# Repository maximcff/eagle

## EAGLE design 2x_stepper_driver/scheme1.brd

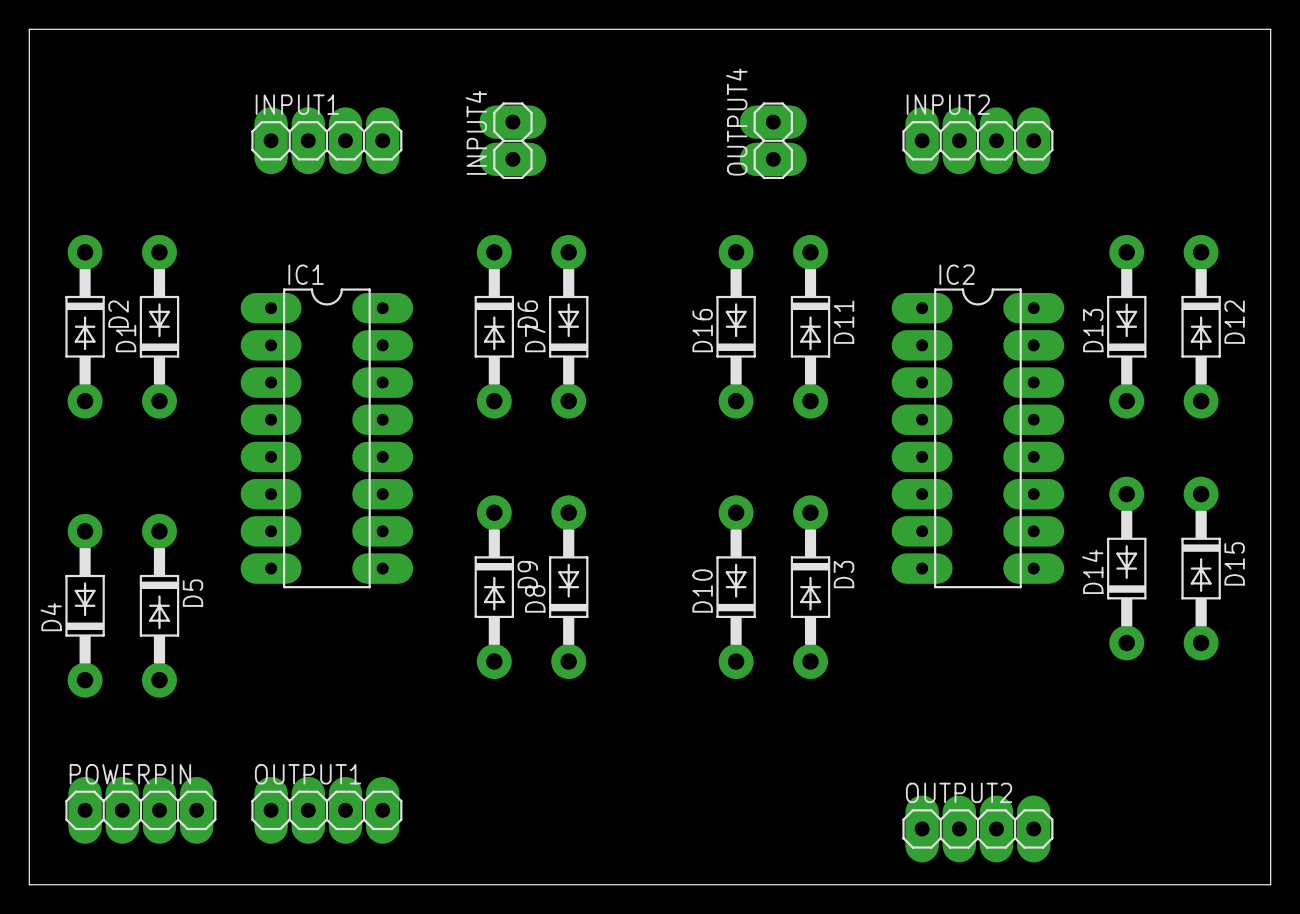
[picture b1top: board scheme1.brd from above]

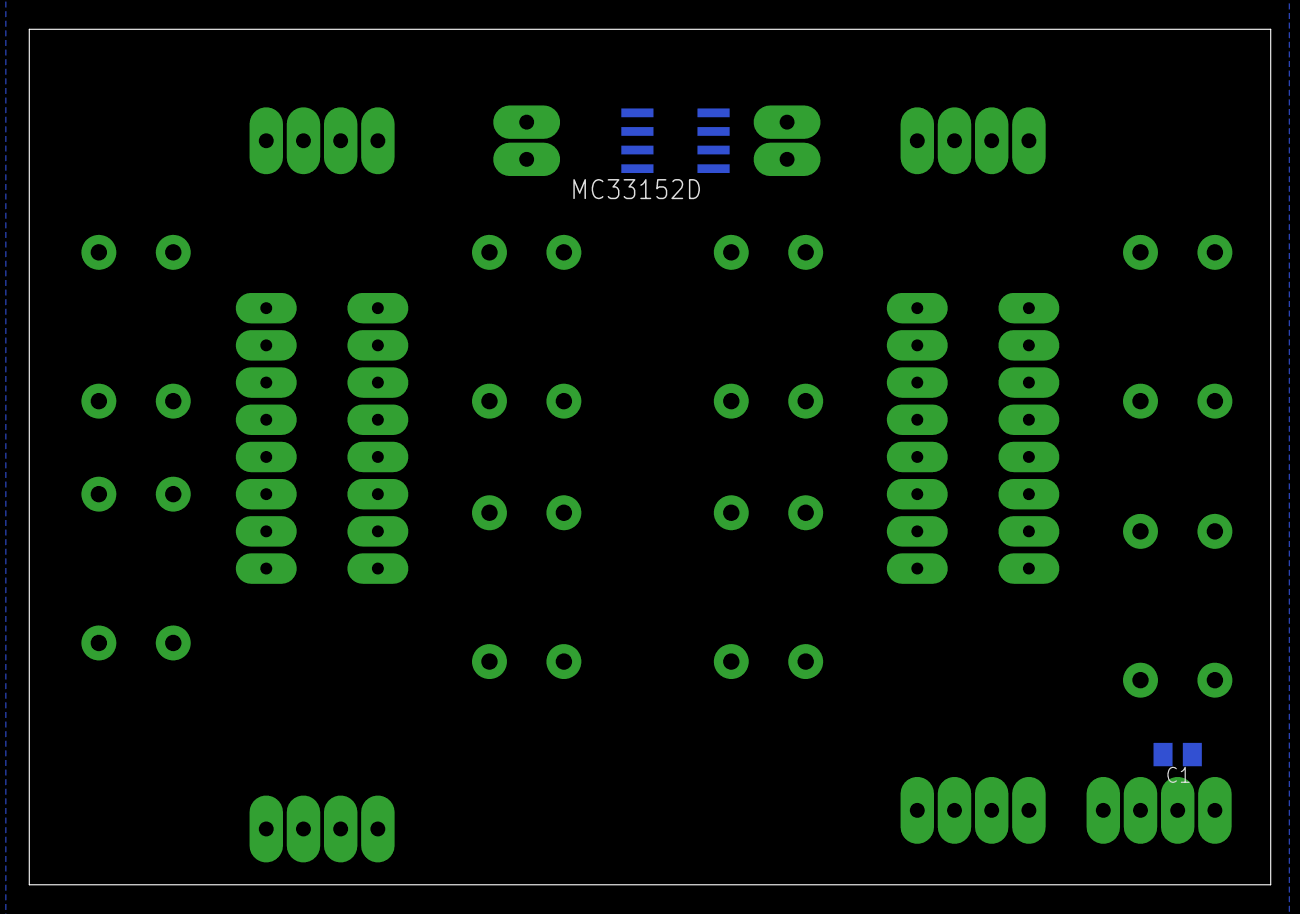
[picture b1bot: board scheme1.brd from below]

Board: 2 copper layers, 84.8 x 58.4 mm, 27 parts (2 on the bottom side), 23 nets, no tracks yet.

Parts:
C1: 0.22 uF; C0805K
D1, D2, D3, D4, D5, D6, D7, D8, D9, D10, D11, D12, D13, D14, D15, D16: 1N4933; DO41-10
IC1, IC2: L293E; DIL16
INPUT1, INPUT2: 1X04
INPUT4: 1X02
MC33152D: MC33152D; SOIC8
OUTPUT1, OUTPUT2: 1X04
OUTPUT4: 1X02
POWERPIN: 1X04

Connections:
+5V: IC1.1, IC1.9, IC1.16, IC2.1, IC2.9, IC2.16, POWERPIN.2
+12V: C1.1, D2.C, D4.C, D6.C, D8.C, D10.C, D11.C, D12.C, D14.C, IC1.8, IC2.8, MC33152D.6, POWERPIN.1
GND: C1.2, D1.A, D3.A, D5.A, D7.A, D9.A, D13.A, D15.A, D16.A, IC1.4, IC1.5, IC1.12, IC1.13, IC2.4, IC2.5, IC2.12, IC2.13, MC33152D.3, POWERPIN.3, POWERPIN.4
IN1: IC1.2, INPUT1.1
IN2: IC1.7, INPUT1.2
IN3: IC1.10, INPUT1.3
IN4: IC1.15, INPUT1.4
IN5: IC2.2, INPUT2.1
IN6: IC2.7, INPUT2.2
IN7: IC2.15, INPUT2.3
IN8: IC2.10, INPUT2.4
IN9: INPUT4.1, MC33152D.2
IN10: INPUT4.2, MC33152D.4
OUT1: D1.C, D2.A, IC1.3, OUTPUT1.1
OUT2: D4.A, D5.C, IC1.6, OUTPUT1.2
OUT3: D8.A, D9.C, IC1.11, OUTPUT1.3
OUT4: D6.A, D7.C, IC1.14, OUTPUT1.4
OUT5: D11.A, D16.C, IC2.3, OUTPUT2.1
OUT6: D3.C, D10.A, IC2.6, OUTPUT2.2
OUT7: D12.A, D13.C, IC2.14, OUTPUT2.3
OUT8: D14.A, D15.C, IC2.11, OUTPUT2.4
OUT9: MC33152D.7, OUTPUT4.1
OUT10: MC33152D.5, OUTPUT4.2

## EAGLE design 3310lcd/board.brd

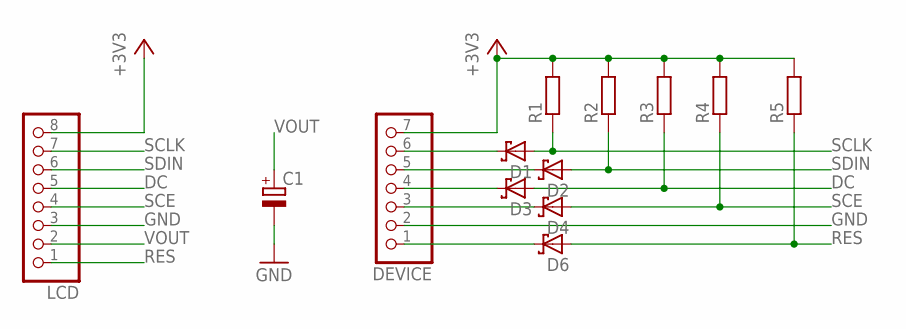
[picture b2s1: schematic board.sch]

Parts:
C1: CPOL-EUE2.5-5; E2,5-5
D1, D2, D3, D4, D6: SCHOTTKY-DIODESMD; SMB
DEVICE: PINHD-1X7; 1X07
LCD: PINHD-1X8; 1X08
R1, R2, R3, R4, R5: R-EU_R0805; R0805

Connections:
+3V3: DEVICE.7, LCD.8, R1.2, R2.2, R3.2, R4.2, R5.2
DC: D3.A, LCD.5, R3.1
GND: C1.-, DEVICE.2, LCD.3
unnamed: D1.C, DEVICE.6
unnamed: D2.C, DEVICE.5
unnamed: D3.C, DEVICE.4
unnamed: D4.C, DEVICE.3
unnamed: D6.C, DEVICE.1
RES: D6.A, LCD.1, R5.1
SCE: D4.A, LCD.4, R4.1
SCLK: D1.A, LCD.7, R1.1
SDIN: D2.A, LCD.6, R2.1
VOUT: C1.+, LCD.2

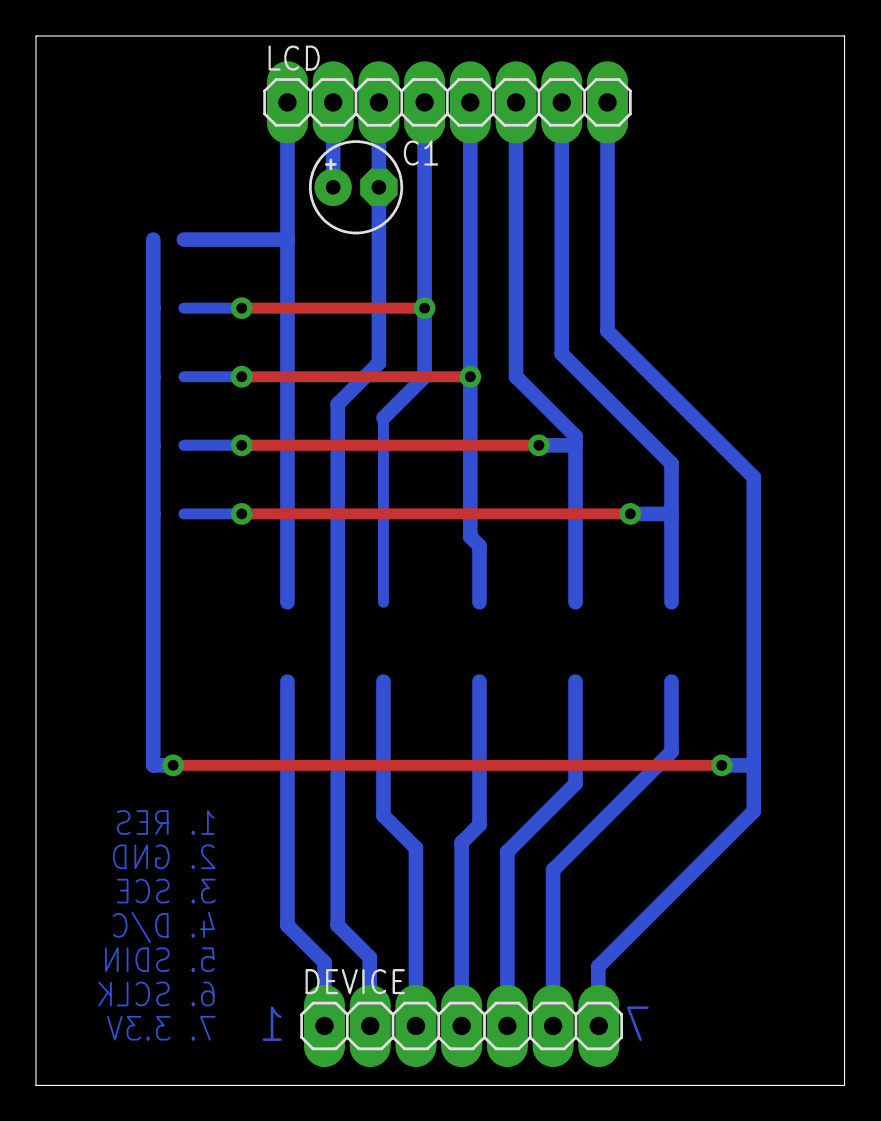
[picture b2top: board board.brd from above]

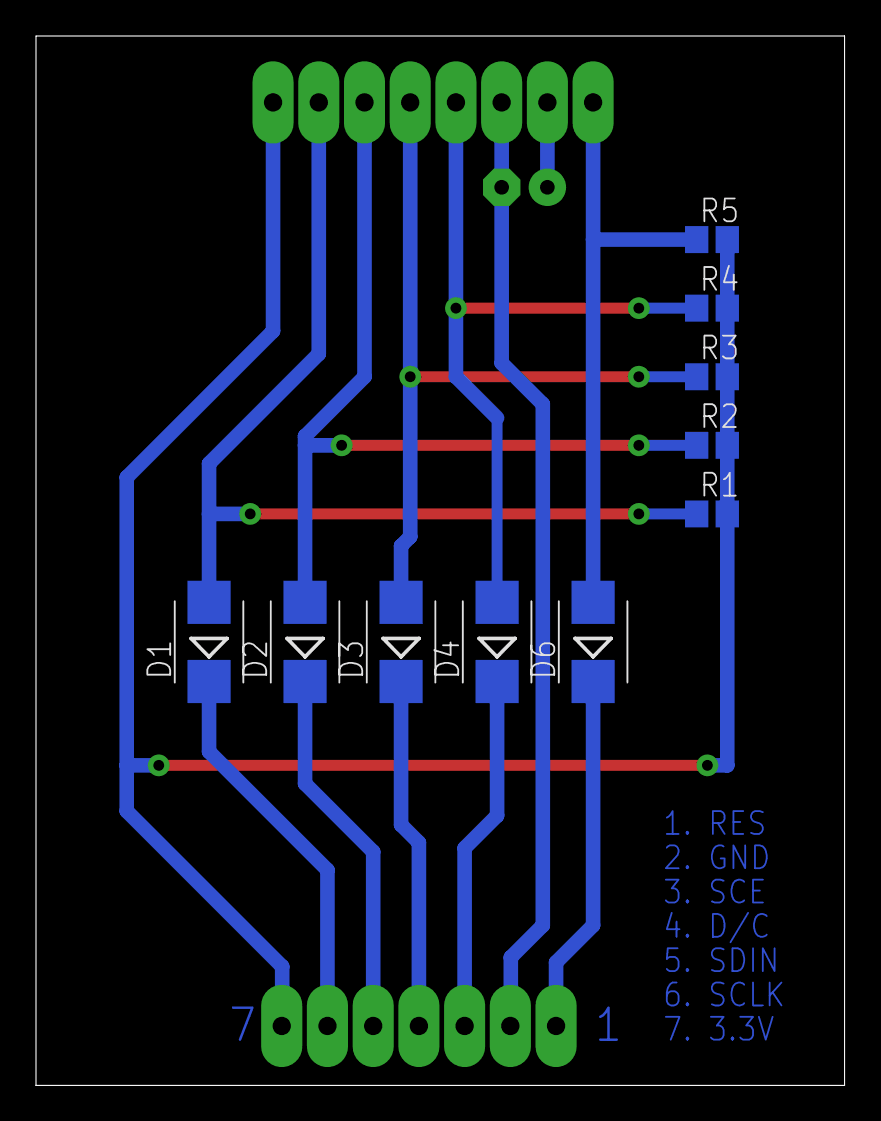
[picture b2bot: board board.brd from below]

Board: 2 copper layers, 44.9 x 58.3 mm, 13 parts (10 on the bottom side), 13 nets.

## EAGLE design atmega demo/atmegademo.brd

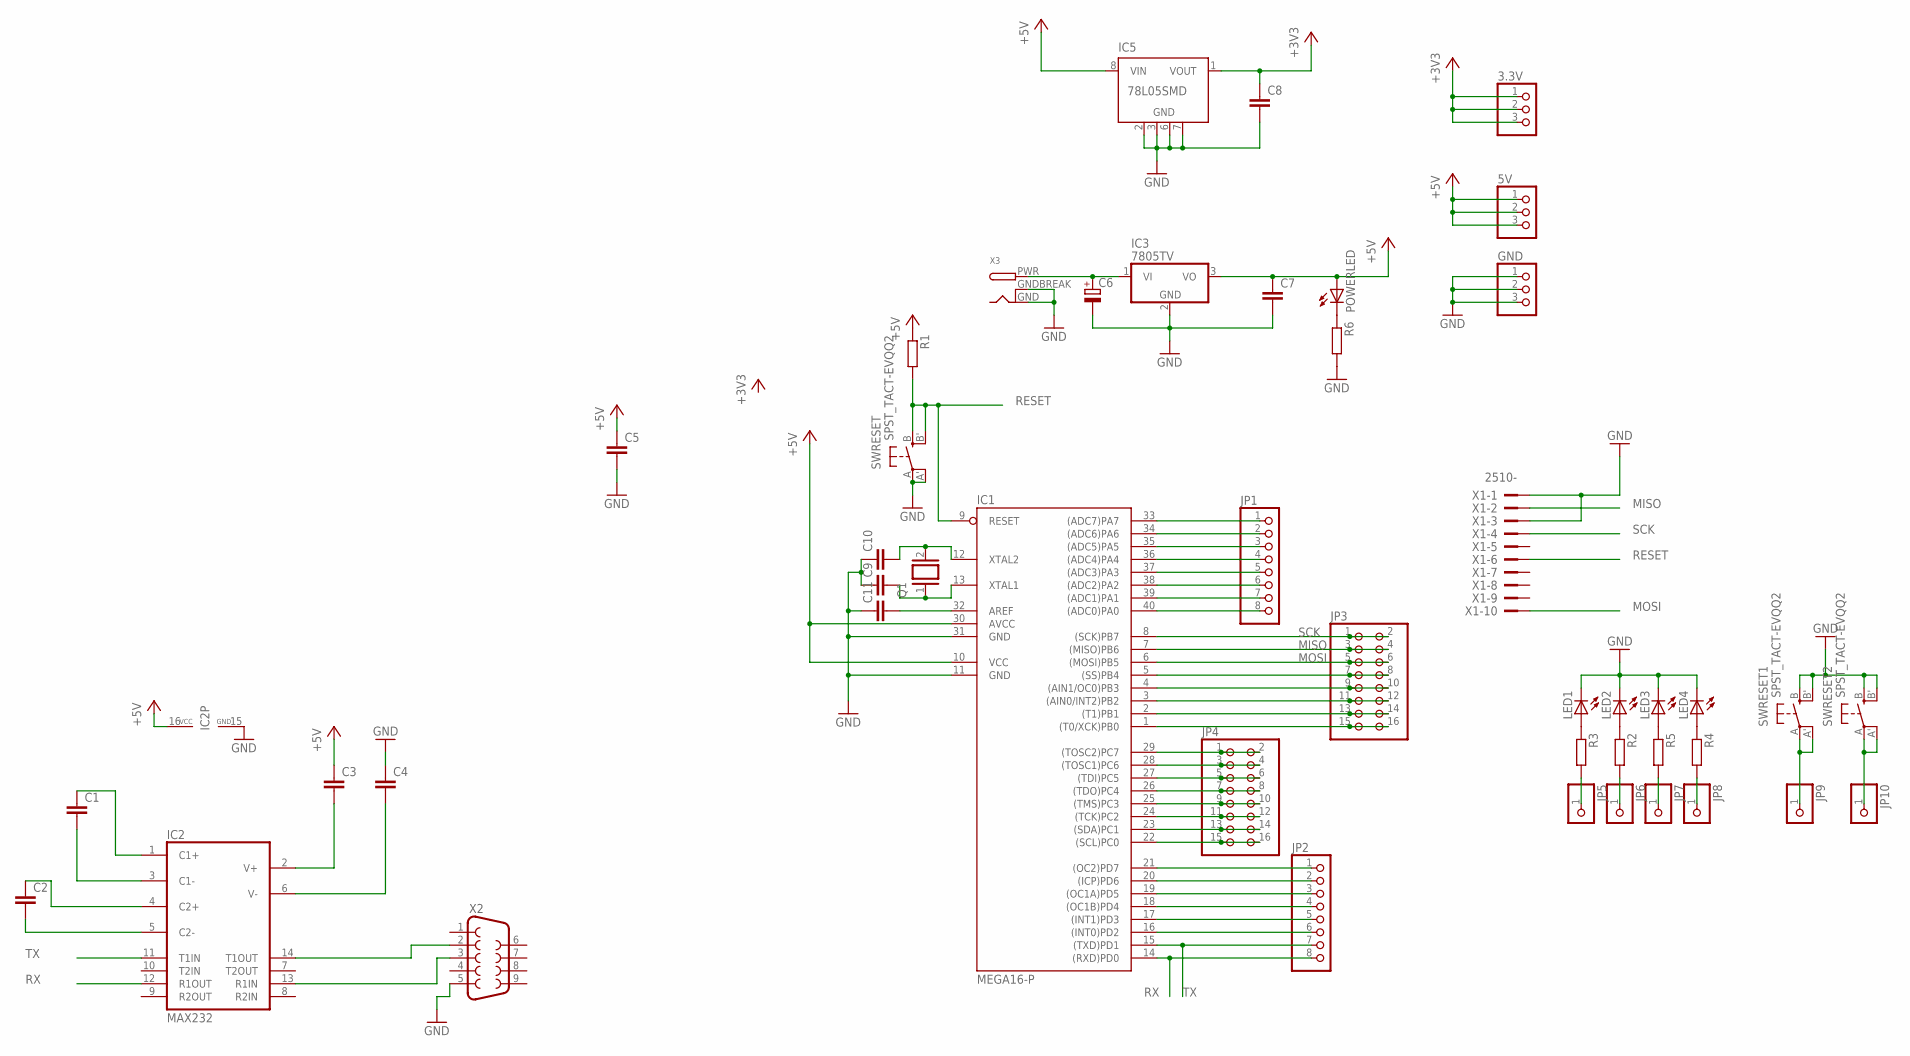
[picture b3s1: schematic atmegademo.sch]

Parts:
3.3V, 5V: PINHD-1X3; 1X03
C1, C2, C3, C4, C5, C7, C8, C11: C-EUC0805K; C0805K
C6: CPOL-EUE2.5-5; E2,5-5
C9, C10: C-EU050-025X075; C050-025X075
GND: PINHD-1X3; 1X03
IC1: MEGA16-P; DIL40
IC2: MAX232; DIL16
IC3: 7805TV; TO220V
IC5: 78L05SMD; SO08
JP1, JP2: PINHD-1X8BIG; 1X08-BIG
JP3, JP4: PINHD-2X8; 2X08
JP5, JP6, JP7, JP8, JP9, JP10: PINHD-1X1; 1X01
LED1, LED2, LED3, LED4: LED3MM
POWERLED: LED3MM
Q1: XTAL/S; QS
R1: R-EU_0207/12; 0207/12
R2, R4: R-EU_R0805; R0805
R3, R5, R6: R-EU_M0805; M0805
SWRESET, SWRESET1, SWRESET2: SPST_TACT-EVQQ2; EVQ-Q2
X1: 2510-; PAK100/2500-10
X2: F09H
X3: DCBARRELPTH; DCJACK_2MM_PTH

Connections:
+3V3: 3.3V.1, 3.3V.2, 3.3V.3, C8.1, IC5.1 (VOUT)
+5V: 5V.1, 5V.2, 5V.3, C3.1, C5.1, C7.1, IC1.10 (VCC), IC1.30 (AVCC), IC2.16 (VCC), IC3.3 (VO), IC5.8 (VIN), POWERLED.A, R1.1
A0: IC1.40 ((ADC0)PA0), JP1.8
A1: IC1.39 ((ADC1)PA1), JP1.7
A2: IC1.38 ((ADC2)PA2), JP1.6
A3: IC1.37 ((ADC3)PA3), JP1.5
A4: IC1.36 ((ADC4)PA4), JP1.4
A5: IC1.35 ((ADC5)PA5), JP1.3
A6: IC1.34 ((ADC6)PA6), JP1.2
A7: IC1.33 ((ADC7)PA7), JP1.1
GND: C4.1, C5.2, C6.-, C7.2, C8.2, C9.1, C10.1, C11.1, GND.1, GND.2, GND.3, IC1.11 (GND), IC1.31 (GND), IC2.15 (GND), IC3.2 (GND), IC5.2 (GND), IC5.3 (GND), IC5.6 (GND), IC5.7 (GND), LED1.K (C), LED2.K (C), LED3.K (C), LED4.K (C), R6.2, SWRESET.A, SWRESET.A' (P1), SWRESET1.B (S), SWRESET1.B' (S1), SWRESET2.B (S), SWRESET2.B' (S1), X1.1, X1.3, X2.5, X3.GND, X3.GNDBREAK
MISO: IC1.7 ((MISO)PB6), JP3.3, JP3.4, X1.2
MOSI: IC1.6 ((MOSI)PB5), JP3.5, JP3.6, X1.10
unnamed: C1.1, IC2.1 (C1+)
unnamed: C1.2, IC2.3 (C1-)
unnamed: C2.1, IC2.4 (C2+)
unnamed: C2.2, IC2.5 (C2-)
unnamed: C3.2, IC2.2 (V+)
unnamed: C4.2, IC2.6 (V-)
unnamed: IC1.21 ((OC2)PD7), JP2.1
unnamed: IC2.13 (R1IN), X2.3
unnamed: IC2.14 (T1OUT), X2.2
unnamed: IC1.20 ((ICP)PD6), JP2.2
unnamed: IC1.19 ((OC1A)PD5), JP2.3
unnamed: IC1.18 ((OC1B)PD4), JP2.4
unnamed: IC1.17 ((INT1)PD3), JP2.5
unnamed: C6.+, IC3.1 (VI), X3.PWR
unnamed: IC1.16 ((INT0)PD2), JP2.6
unnamed: IC1.4 ((AIN1/OC0)PB3), JP3.9, JP3.10
unnamed: IC1.3 ((AIN0/INT2)PB2), JP3.11, JP3.12
unnamed: IC1.2 ((T1)PB1), JP3.13, JP3.14
unnamed: IC1.1 ((T0/XCK)PB0), JP3.15, JP3.16
unnamed: IC1.29 ((TOSC2)PC7), JP4.1, JP4.2
unnamed: IC1.28 ((TOSC1)PC6), JP4.3, JP4.4
unnamed: IC1.5 ((SS)PB4), JP3.7, JP3.8
unnamed: LED1.A, R3.1
unnamed: LED2.A, R2.1
unnamed: IC1.27 ((TDI)PC5), JP4.5, JP4.6
unnamed: IC1.26 ((TDO)PC4), JP4.7, JP4.8
unnamed: IC1.25 ((TMS)PC3), JP4.9, JP4.10
unnamed: LED4.A, R4.1
unnamed: LED3.A, R5.1
unnamed: IC1.24 ((TCK)PC2), JP4.11, JP4.12
unnamed: IC1.23 ((SDA)PC1), JP4.13, JP4.14
unnamed: IC1.22 ((SCL)PC0), JP4.15, JP4.16
unnamed: JP5.1, R3.2
unnamed: JP6.1, R2.2
unnamed: POWERLED.K (C), R6.1
unnamed: JP7.1, R5.2
unnamed: JP8.1, R4.2
unnamed: C10.2, IC1.12 (XTAL2), Q1.2
unnamed: C9.2, IC1.13 (XTAL1), Q1.1
unnamed: JP9.1, SWRESET1.A, SWRESET1.A' (P1)
unnamed: C11.2, IC1.32 (AREF)
unnamed: JP10.1, SWRESET2.A, SWRESET2.A' (P1)
RESET: IC1.9 (RESET), R1.2, SWRESET.B (S), SWRESET.B' (S1), X1.6
RX: IC1.14 ((RXD)PD0), IC2.12 (R1OUT), JP2.8
SCK: IC1.8 ((SCK)PB7), JP3.1, JP3.2, X1.4
TX: IC1.15 ((TXD)PD1), IC2.11 (T1IN), JP2.7

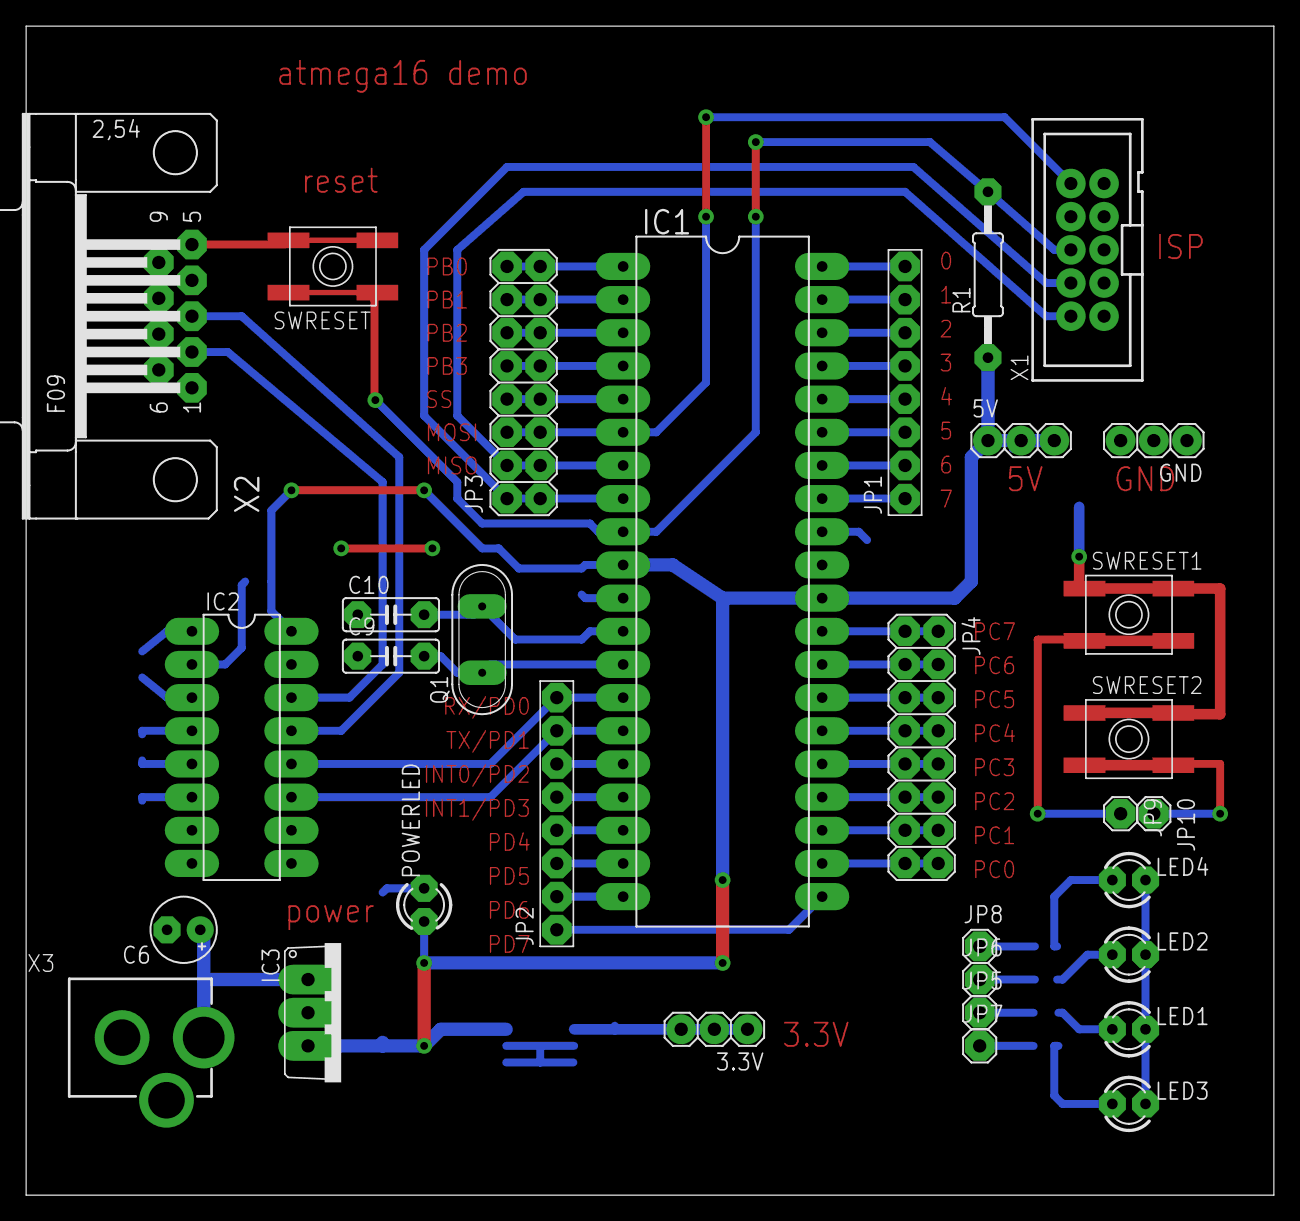
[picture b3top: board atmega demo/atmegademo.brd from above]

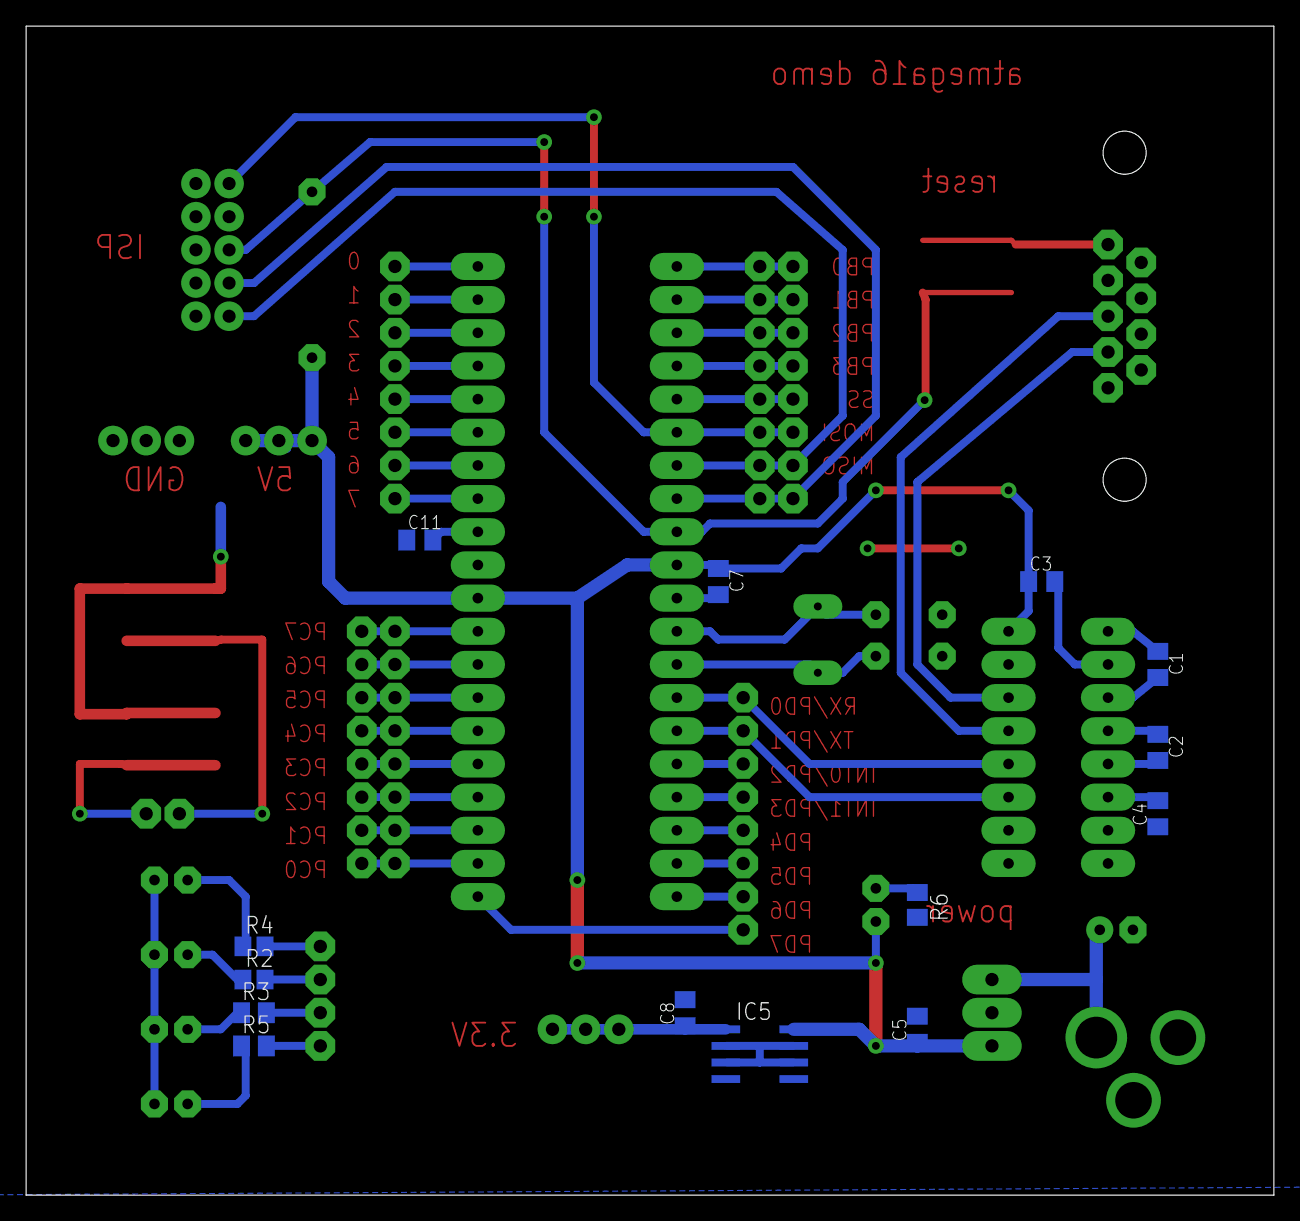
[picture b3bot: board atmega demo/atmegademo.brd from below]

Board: 2 copper layers, 95.6 x 89.5 mm, 46 parts (14 on the bottom side), 59 nets.

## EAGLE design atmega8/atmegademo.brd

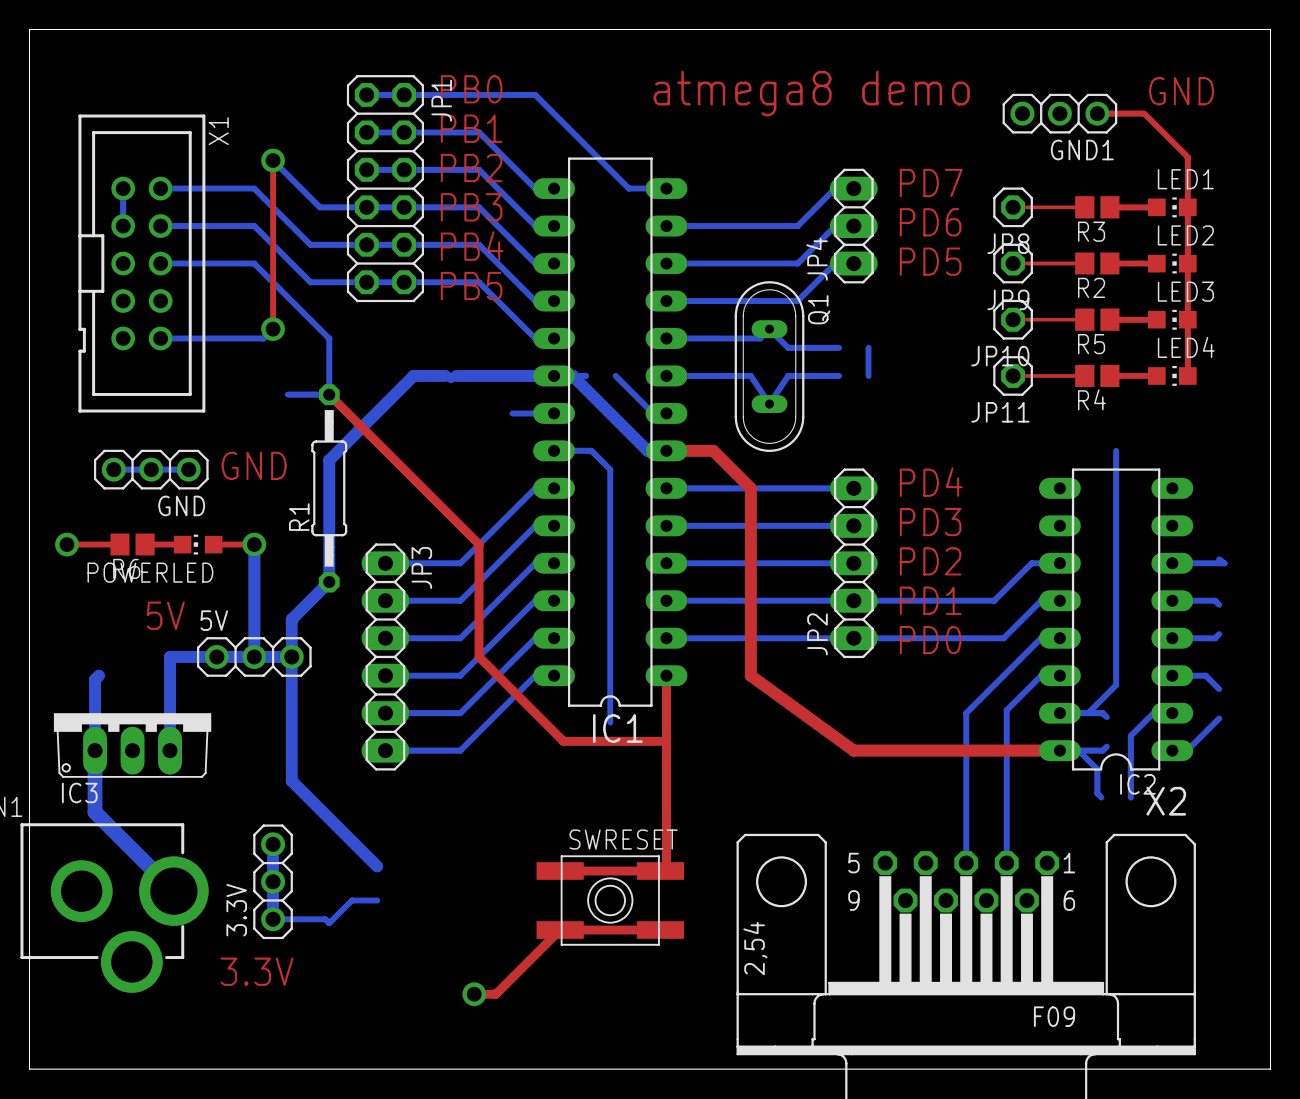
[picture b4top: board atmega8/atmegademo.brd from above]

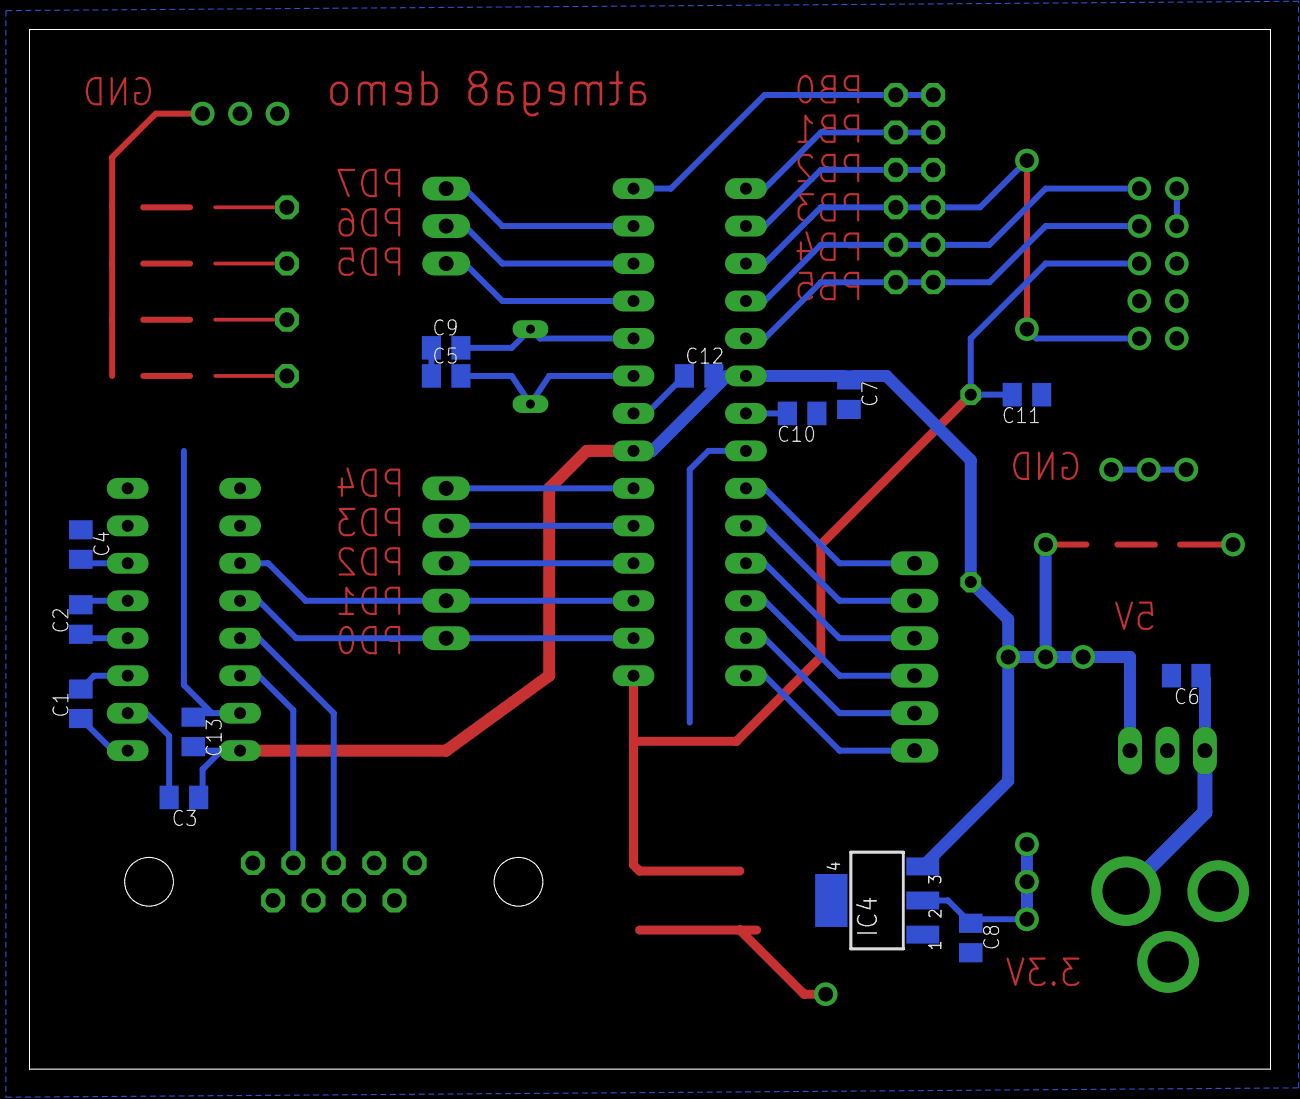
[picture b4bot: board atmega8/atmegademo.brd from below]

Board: 2 copper layers, 84.1 x 70.5 mm, 45 parts (14 on the bottom side), 45 nets.

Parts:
3.3V, 5V: 1X03
C1, C2, C3, C4, C5, C6, C7, C8, C9, C10, C11, C12, C13: C0805K
CN1: DCJACK_2MM_PTH
GND, GND1: 1X03
IC1: MEGA8-P; DIL28-3
IC2: MAX232; DIL16
IC3: 7805TV; TO220V
IC4: 317EMP; SOT223
JP1: 2X06
JP2: 1X05
JP3: 1X06
JP4: 1X03
JP8, JP9, JP10, JP11: 1X01
LED1, LED2, LED3, LED4: CHIP-LED0805
POWERLED: CHIP-LED0805
Q1: QS
R1: 0207/12
R2, R3, R4, R5, R6: R0805
SWRESET: SPST_TACT-EVQQ2; EVQ-Q2
X1: 2510-; PAK100/2500-10
X2: F09H

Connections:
+3V3: 3.3V.1, 3.3V.2, 3.3V.3, C8.1, IC4.2
+5V: 5V.1, 5V.2, 5V.3, C3.1, C7.1, C12.2, C13.2, IC1.7, IC1.20, IC2.16, IC3.3, IC4.3, POWERLED.A, R1.1
GND: C4.1, C5.1, C6.2, C7.2, C8.2, C9.1, C10.1, C11.1, C12.1, C13.1, CN1.GND, CN1.GNDBREAK, GND.1, GND.2, GND.3, GND1.1, GND1.2, GND1.3, IC1.8, IC1.22, IC2.15, IC3.2, IC4.1, LED1.C, LED2.C, LED3.C, LED4.C, R6.2, SWRESET.A, SWRESET.A', X1.1, X1.3, X2.5
MISO: IC1.18, JP1.9, JP1.10, X1.2
MOSI: IC1.17, JP1.7, JP1.8, X1.10
unnamed: C1.1, IC2.1
unnamed: C1.2, IC2.3
unnamed: C2.1, IC2.4
unnamed: C2.2, IC2.5
unnamed: C3.2, IC2.2
unnamed: C4.2, IC2.6
unnamed: JP8.1, R3.2
unnamed: IC2.13, X2.3
unnamed: IC2.14, X2.2
unnamed: JP9.1, R2.2
unnamed: IC1.4, JP2.3
unnamed: IC1.5, JP2.4
unnamed: IC1.6, JP2.5
unnamed: C6.1, CN1.PWR, IC3.1
unnamed: IC1.11, JP4.1
unnamed: IC1.23, JP3.1
unnamed: IC1.12, JP4.2
unnamed: IC1.13, JP4.3
unnamed: IC1.24, JP3.2
unnamed: IC1.25, JP3.3
unnamed: IC1.26, JP3.4
unnamed: JP10.1, R5.2
unnamed: LED1.A, R3.1
unnamed: LED2.A, R2.1
unnamed: JP11.1, R4.2
unnamed: C10.2, IC1.21
unnamed: C5.2, IC1.9, Q1.2
unnamed: LED4.A, R4.1
unnamed: LED3.A, R5.1
unnamed: C9.2, IC1.10, Q1.1
unnamed: IC1.15, JP1.3, JP1.4
unnamed: IC1.16, JP1.5, JP1.6
unnamed: IC1.14, JP1.1, JP1.2
unnamed: POWERLED.C, R6.1
RESET: C11.2, IC1.1, R1.2, SWRESET.B, SWRESET.B', X1.6
RX: IC1.2, IC2.12, JP2.1
SCK: IC1.19, JP1.11, JP1.12, X1.4
SCL: IC1.28, JP3.6
SDA: IC1.27, JP3.5
TX: IC1.3, IC2.11, JP2.2

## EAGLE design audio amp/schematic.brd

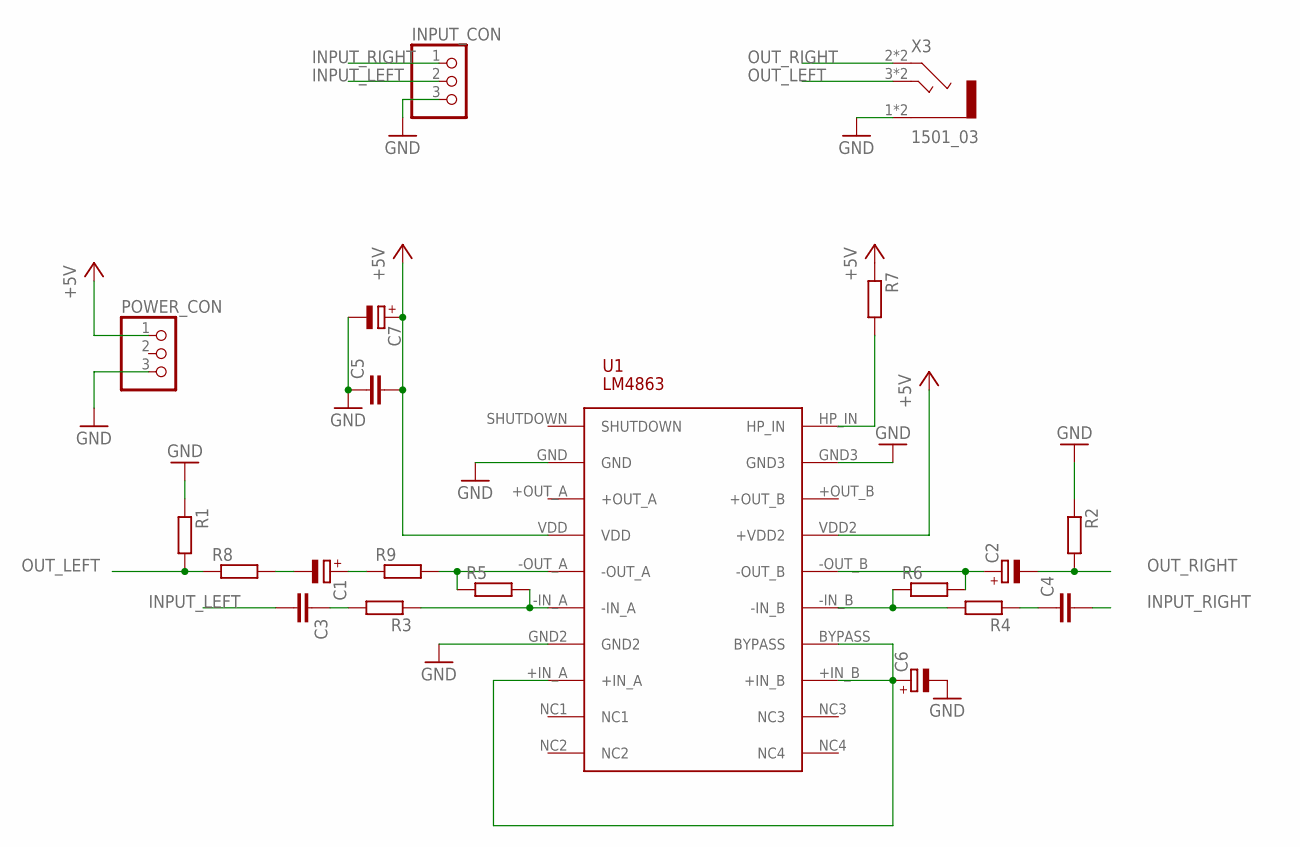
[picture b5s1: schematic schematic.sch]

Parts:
C1, C2, C6, C7: CPOL-EUE2.5-7; E2,5-7
C3, C4: C-EU050-035X075; C050-035X075
C5: C-EU050-024X044; C050-024X044
INPUT_CON: PINHD-1X3CB; 1X03-CLEANBIG
POWER_CON: PINHD-1X3; 1X03
R1, R4, R6: R-EU_0207/2V; 0207/2V
R2, R3, R7: R-EU_0207/10; 0207/10
R5: R-EU_0204/2V; 0204V
R8, R9: R-EU_0204/7; 0204/7
U1: LM4863; TSSOP20
X3: 1501_03

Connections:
+5V: C5.2, C7.+, POWER_CON.1, R7.1, U1.VDD, U1.VDD2 (+VDD2)
GND: C5.1, C6.-, C7.-, INPUT_CON.3, POWER_CON.3, R1.1, R2.1, U1.GND, U1.GND2, U1.GND3, X3.1, X3.11 (1)
INPUT_LEFT: C3.2, INPUT_CON.2
INPUT_RIGHT: C4.2, INPUT_CON.1
unnamed: C2.+, R6.2, U1.-OUT_B
unnamed: R5.1, R9.2, U1.-OUT_A
unnamed: C3.1, R3.2
unnamed: R3.1, R5.2, U1.-IN_A
unnamed: R4.2, R6.1, U1.-IN_B
unnamed: C4.1, R4.1
unnamed: C6.+, U1.+IN_A, U1.+IN_B, U1.BYPASS
unnamed: R7.2, U1.HP_IN
unnamed: C1.-, R8.2
unnamed: C1.+, R9.1
OUT_LEFT: R1.2, R8.1, X3.3, X3.33 (3)
OUT_RIGHT: C2.-, R2.2, X3.2, X3.22 (2)

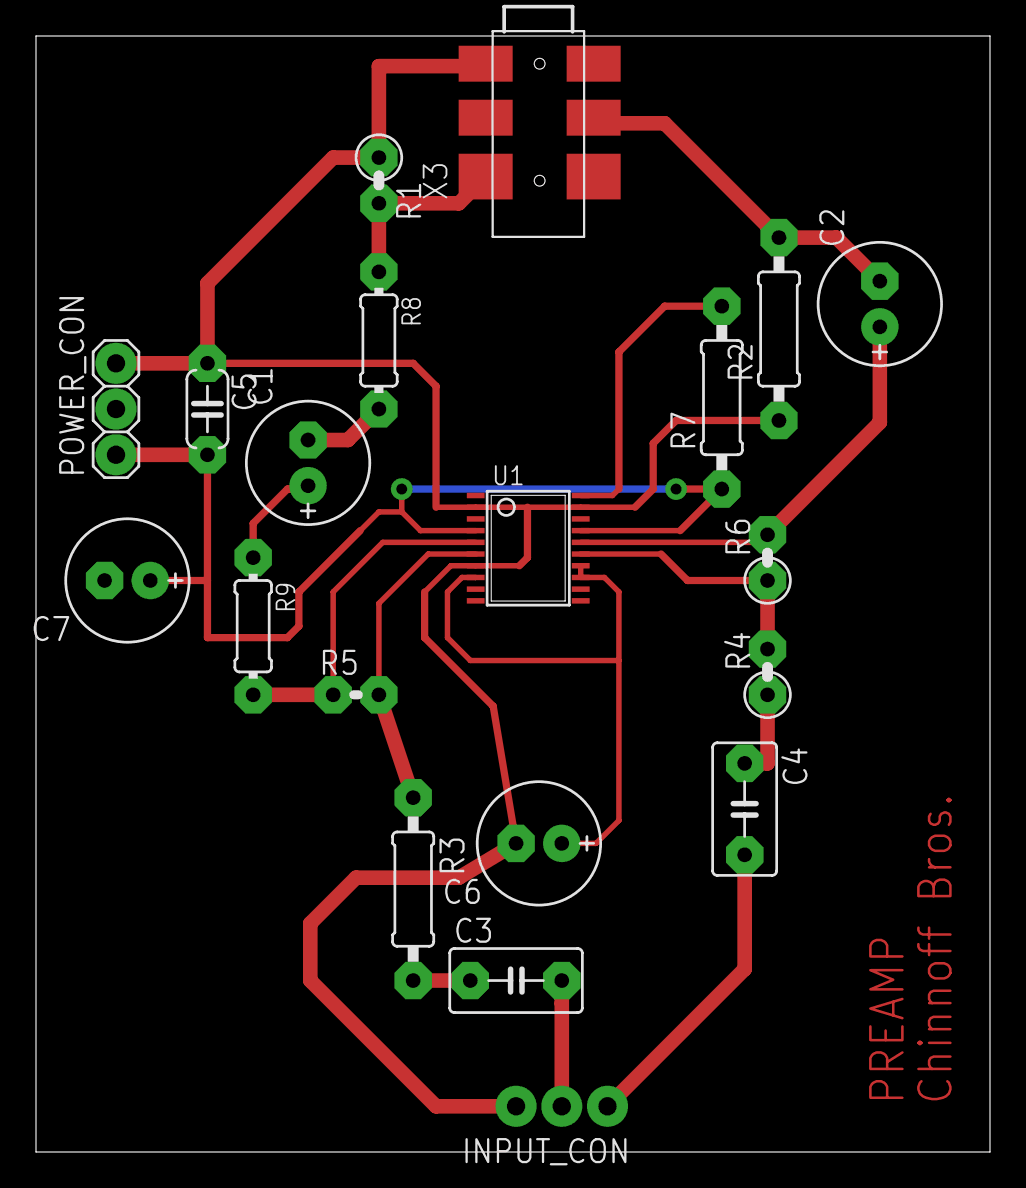
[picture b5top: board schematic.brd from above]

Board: 2 copper layers, 53.0 x 62.0 mm, 20 parts (0 on the bottom side), 16 nets.

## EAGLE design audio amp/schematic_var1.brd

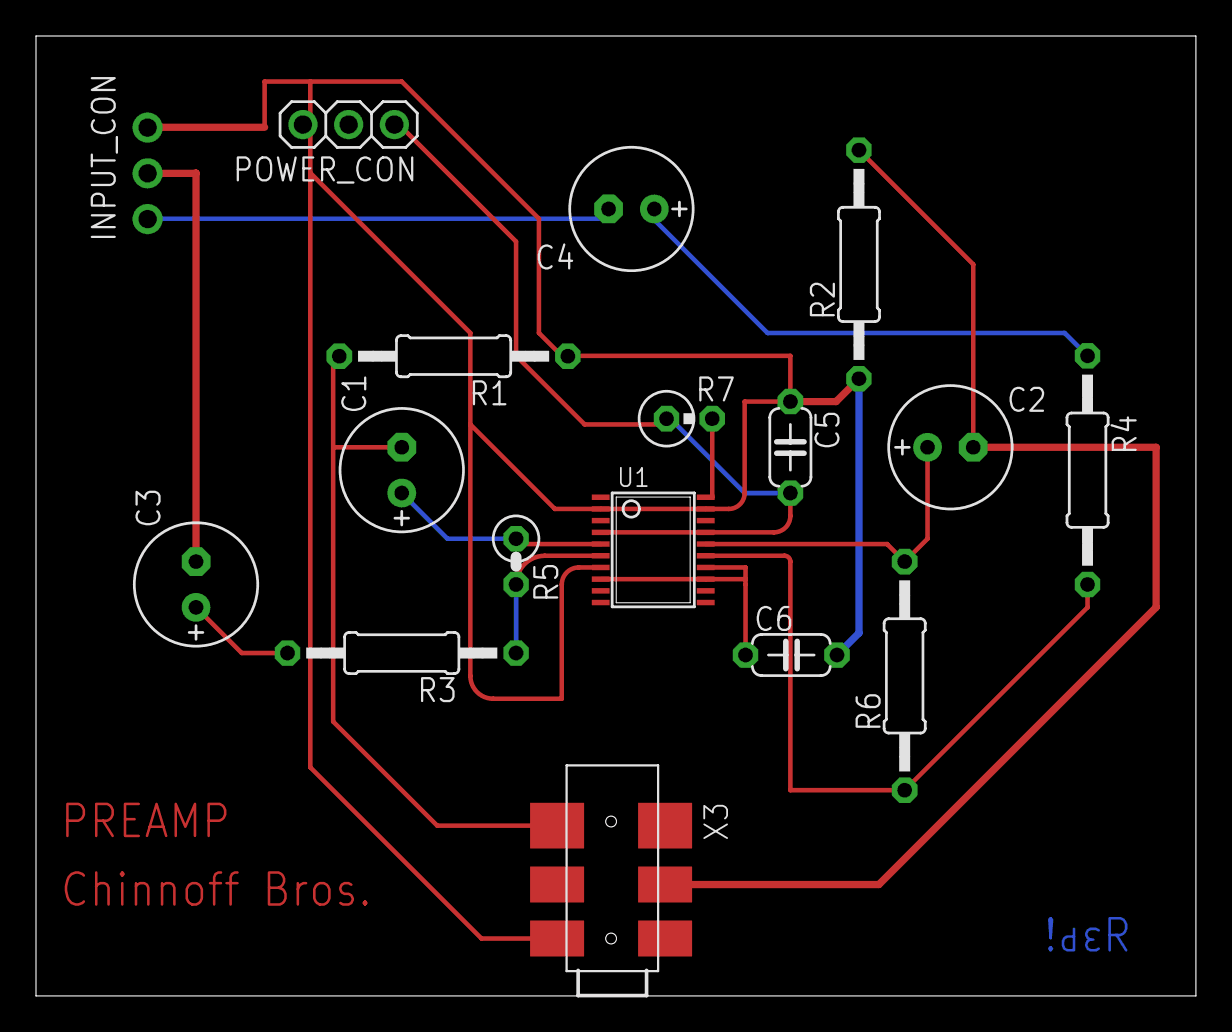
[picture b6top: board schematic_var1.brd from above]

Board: 2 copper layers, 64.4 x 53.3 mm, 17 parts (0 on the bottom side), 14 nets.

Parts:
C1, C2, C3, C4: E2,5-7
C5, C6: C050-024X044
INPUT_CON: 1X03-CLEANBIG
POWER_CON: 1X03
R1, R2, R3, R4, R6: 0207/12
R5: 0207/2V
R7: 0309V
U1: LM4863; TSSOP20
X3: 1501_03

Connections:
+5V: C5.2, POWER_CON.1, R7.1, U1.VDD, U1.VDD2
GND: C5.1, C6.2, INPUT_CON.3, POWER_CON.3, R1.1, R2.1, U1.GND, U1.GND2, U1.GND3, X3.1
INPUT_LEFT: C3.-, INPUT_CON.2
INPUT_RIGHT: C4.-, INPUT_CON.1
unnamed: C2.+, R6.2, U1.-OUT_B
unnamed: C1.+, R5.1, U1.-OUT_A
unnamed: C3.+, R3.2
unnamed: R3.1, R5.2, U1.-IN_A
unnamed: R4.2, R6.1, U1.-IN_B
unnamed: C4.+, R4.1
unnamed: C6.1, U1.+IN_A, U1.+IN_B, U1.BYPASS
unnamed: R7.2, U1.HP_IN
OUT_LEFT: C1.-, R1.2, X3.3
OUT_RIGHT: C2.-, R2.2, X3.22
